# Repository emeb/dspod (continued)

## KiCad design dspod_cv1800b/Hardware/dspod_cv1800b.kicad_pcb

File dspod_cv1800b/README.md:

# dspod_cv1800b

The dspod_cv1800b is a daughterboard comprising a Sophgo/CVItek CV1800B Linux SoC with 64MB RAM, SD card interface, USB and GPIO + audio I/O.

## Abstract

This project was inspired by the release of the Milk-V Duo development board for the Sophgo/CVItek CV1800B SoC back in late 2023. The main chip is a 1GHz dual-core RISC-V system with integrated DRAM in a DIY-friendly 68-pin QFN package that would allow me to build a single-board audio DSP module at low cost without needing fancy PCB processes of complex assembly. I spent a fair amount of time exploring the hardware and OS before concluding that I would be able to tweak it to my requirements, but after getting the basic interfaces working on the Duo board it decided to roll my own.

The board is a small 32-pin device with the following features:

* CV1800B Linux SoC
  - 1GHz RISC-V primary CPU
  - 700MHz RISC-V secondary CPU
  - 8051 low-power CPU
  - 64MB SDRAM~~~~
  - 0.5 TOPS NPU
  - 68-pin QFN package
* Micro SD card slot
* USB-C connector
* Nuvoton NAU88C22 stereo codec
* Misc GPIO
  - SPI
  - I2C
  - GPIO
* Four channels of 3.3V multiplexed A/D input

## Design Materials

* [Schematic](./doc/dspod_cv1800b_schematic.pdf) (PDF)
* [Bill of Materials](./doc/dspod_cv1800b_BOM.ods) (in LibreOffice Calc spreadsheet format)

## Hardware

 Schematic and board design were done with Kicad 9.x and the project is available in the [Hardware](./Hardware/) directory.

## Software

The CV1800B SoC runs a Buildroot / Busybox version of Linux based on a 5.10 kernel
with vendor-customized extensions (not upstreamed). The vendor SDK is freely
available here [Milk-V SDK V2](https://github.com/milkv-duo/duo-buildroot-sdk-v2)

I've customized the kernel with drivers and device-tree configurations that are
specific to this board. My fork of the SDK is here
[Customize kernel SDK](https://github.com/emeb/duo-buildroot-sdk-v2/tree/audio_board)

Additionally, there is a user-space application that provides the UI for the board
along with drivers for the audio codec and 4-channel ADC - find the source here
[dspod app](https://github.com/emeb/duo-examples/tree/main/dspod_app)

## Results

Building an audio DSP module based on the CV1800B SoC was the primary motivation for the dspod project so this 'pod' was the first one that got the full suite of features implemented. The dspod_app software mentioned above has all the features working:

- Stereo audio I/O

- 4 channel CV input

- LCD + encoder based UI

Getting all this working under the Milk-V SDK V2 has been an interesting experience. A few of the things I learned:

#### Audio I/O

This required a fair bit of effort because the pins on the SoC used for I2S audio are the same ones used by the ethernet port, so there was a lot of fiddling around with U-Boot pinmuxing and hidden, poorly-documented control registers to switch those pins over to I2S function. Additionally the I2S MCLK needed by the codec chip had to be stolen from another pin that appeared to be in use (it actually wasn't) and that also required some careful reading of the SoC reference manual to determine that the clock on that pin would actually work. There wasn't really much in the way of kernel shenannigans necessary, but I did have multiple iterations of fiddling with Device Tree to get the I2S drivers hooked up properly.

Eventually I got it all working and it's been very reliable since then. The low-level SoC audio device drivers have been trouble-free and accessing them via ALSA works just like it does on other embedded Linux platforms I've worked with.

#### ADC

I decided to use the on-chip ADC for sampling the four control voltage channels that the dspod design needs, but only two of the three possible channels are brought out to pins on the SoC so an external analog multiplexer was needed. The kernel driver for the ADC is available in both the V1 and V2 SDKs and there’s a nice example available as well so I was able to get it running and learned a few things:

- The existing kernel driver is incomplete - it has interfaces for both the usual char device in the /dev directory and a sysfs entry, but the char device read() function will not work as it doesn’t pass its value back to the caller’s buffer. The sysfs show() function on the other hand returns its value as an ASCII string with a decimal numeric value which is easy to read when you just ‘cat’ the file from the command line but requires you to convert it back to an integer so it’s a bit cumbersome to use within a program.
- The read() and show() functions are similar in that they trigger a conversion and then wait while the ADC is busy before reading the result and returning it. The problem here is that they busywait inside a spinlock_irqsave() so the entire kernel is blocked for 20us while waiting for the conversion. This may be OK if you’re only doing conversions occasionally, but it can seriously hamper performance if conversions are requested frequently.

Because of these issues, I’ve modified the driver to get the read() operation to return a binary value and also digging deeper into how to avoid hogging the system during conversions. There is an IRQ available for the end-of-conversion and I use that, along with delay functions that yield to the kernel scheduler to avoid the use of spinlocks. I’ve also added some logic to control the external analog MUX via GPIO directly from the driver and this is working well.

The hardware aspect of the ADC seems fine - the datasheet doesn’t go into much detail how it works, but from the register map I’ve been able to infer a lot of the details and it seems sane. Overall performance of the converter isn’t great however - I see a fair amount of sample-to-sample noise with a standard deviation of about 5 lsbs near max input range but I suppose that’s to be expected on a complex SoC like this and by applying some heavy filtering in software the results are usable if not particularly accurate. I'm pretty sure this noise is inherent in the hardware as I see similar behavior on the Milk-V Duo board.

#### Encoder

The rotary encoder with pushbutton was a breeze to connect. Some simple additions to the Device tree had it working with no drama and the user-space interface via input events is easy to use and well described.

#### LCD

The dspod module provides a SPI-connected 320x170 IPS LCD based on the ST7789 controller chip. The display is sharp and bright with a good viewing angle and is well supported by the Linux kernel 'fbtft' driver (after some minor modifications to the way the reset line is driven). Getting it working requires a small amount of Device Tree work but for the most part that was not too difficult to set up. Accessing the display from user space is straight-forward and well described with example code from various demos on the internet so I had no difficulty creating a shim layer to work with my personal lightweight graphics suite that allows basic drawing primitives and color manipulation.

Creating a responsive user interface on top of this graphics layer was not difficult, but running it in real-time with the audio and ADC drivers running simultaneously did reveal some "non-ideal behavior" - making near-simultaneous changes to the display buffer in regions that are widely separated in pixel distance can result in significant "behind-the scenes" activity within the fbdev kernel driver as it attempts to update large portions of the display. I found that restricting the amount of screen real-estate that is updated at one time reduced the overall CPU load considerably - just insert some delay time between drawing operations to allow smaller regions to be updated.

#### DSP performance

The proof of the pudding is in the way this system handles the DSP needed for generating audio effects. I have a large library of effects from previous work I've done in the field so I set about trying them out on this system.

###### Time Domain

I "ported" most of my library of interesting time-domain audio effects over to this environment, including the following:

- "Clean delay" - delay with no resampling, just crossfade splicing as the delay is changed.

- "Resampled delay" - delay with sinc-based resampling over an 8:1 range for FM effects.

- Frequency shifter - Bode style I/Q modulation with Hilbert transform filters for generating 90deg phase shifts in real signals for non-harmonically scaled changes in frequency.

- Interpolating delay - similar to clean delay but with inter-sample interpolation and fractional delay values lag-filtered to prevent glitching.

- Phaser - all-pass filter banks for group-delay variations with movable notches.

- Flanger - short fractional delays for group-delay variations with movable notches.

- Pitch shifter - granular delays with variable playback ratios for harmonic-scaled changes in frequency.

- Reverbs - several different types, including an emulation of the venerable MIDIverb for algorithmic simulations of natural spaces.

All of these effects worked as expected with no noticeable glitching or discontiuities in the audio caused by background processes in the Linux operating system and typical CPU loading seen during the worst-case reverb algorithms was about 15%.

###### Frequency Domain

Frequency (or "Spectral") effects rely on the Fast-Fourier Transform (FFT) to convert audio samples into 'bins' of discrete frequency magnitude and phase. The FFT is a fairly math-intensive algorithm and for every buffer of audio it's necessary to perform a forward and reverse transform with the unique spectral algorithm sandwiched between the two. I have a collection of interesting algorithms based on a method called "phase vocoder" that were developed on the [Synthesis Technology - Eurorack E520](https://synthtech.com/eurorack/E520/) and run on the [STM32H743](https://www.st.com/en/microcontrollers-microprocessors/stm32h743-753.html) MCU (a 480MHz Arm Cortex M7 CPU) using the FFT algorithms provided by the Arm CMSIS DSP library. The CMSIS FFT will not run on the CV1800B SoC so I needed to find an alternative and after some research I settled on the [pffft](https://bitbucket.org/jpommier/pffft/src/master/) open-source FFT library which has a reputation for reasonably good performance.

I was able to bring the basic transform processing up on the CV1800B under Linux without difficulty and some benchmarking suggested the 4096-point transform I needed would run in about 1ms - well within the 10ms/buffer that I had available. Given two transforms, the phase vocoder and any unique processing required it seemed there would be enough CPU cycles to get some spectral effects going and the load calculations in my audio test harness showed that basic forward + reverse transforms were taking about 27% of the CPU. Unfortunately the combination of all the I/O, UI and DSP plus background processing for the whole system pushed the total load to over 50% which caused time-critical audio I/O processing to miss its schedule and quickly hang the processor.

Things were looking pretty grim for a while and it seemed like there was no way to get my frequency domain algorithms working on this platform but then an old friend with vastly more experience in embedded Linux came to the rescue. Vlad of [VPME.de](https://vpme.de/) has worked on consumer-grade Linux-based media players and suggested some simple tweaks to the way I was handling my audio thread that boosted its priority above the other things going on and I've now had CPU loads in excess of 50% running for hours without errors. Experience counts!

###### FFT optimization

Initially I had chosen pffft to handle the transforms required for spectral effects, partly because it was well regarded in the open source community, but also because it had SIMD support for several architectures (x86, Arm NEON and PPC Altivec) which led me to believe that it would be easily converted to the RISC-V vector extensions aka [RVV](https://riscv.org/wp-content/uploads/2024/12/15.20-15.55-18.05.06.VEXT-bcn-v1.pdf) which are available on the CV1800B SoC. During testing of pffft I saw approx 30% speedup on x86 when enabling SIMD and was hoping for similar gains with RVV. Unfortunately, the architecture of RVV is sufficiently different from older SIMD implementations that adding it to pffft would have been a large undertaking so instead I looked at simpler FFT libraries that might be more easily modified. After hunting for a while I came back to the original Arm CMSIS DSP library that had been used on the STM32. Benchmarking these against pffft I discovered that for a 4k transform, the radix-4 core with loop unrolling enabled provides about a 30% improvement. Starting with this I experimented with some simple vector optimizations and found that the scalar math used in the radix-4 butterfly was already highly streamlined and my attempts to vectorize it just made it worse. As it stands now I'm seeing the 4k FFT/IFFT running in under 600us which is fast enough to support the spectral effects with sufficient headroom.

###### DSP Summary

With proper understanding of the finer points of Linux userspace coding, the CV1800B SoC under Linux works fine for audio effects in both time and frequency domains. There are still some optimizations that may help to attain even greater processor loads than those seen on the simpler frequency domain algorithms I've tested so far:

- Explore further ways to optimize the FFT algorithm to take advantage of RVV. My first forays into this were naive and didn't pan out, but more clever approaches might improve matters. There have been reports that RVV could provide significant gains for FFTs, but details of these studies are not publicly available at this time.

- Study the possibilities of using the NPU provided on the SoC. The CV1800B has a 0.5 TOPS neural processing unit that supports int8 data. While it's primarily intended for video analysis tasks, with sufficiently clever handling it might be applied to audio DSP as well. There is very little documentation available, but plenty of source code for the examples provided by the manufacturer.

- Move the DSP operations onto the currently unused secondary RISC-V core. That core runs at only 700MHz but would be completely free of any other critical loads beyond handling the crucial computations and so might provide an overall performance boost.

- Abandon Linux altogether and run "bare metal" - there are already some open-source attempts to create a build environment to explore this option. It will be an uphill battle due to lack of comprehensive documentation on the hardware resources, but if possible would lead to the most optimum environment for running realtime DSP.

I'll continue to pursue these and other avenues to improve the situation on the CV1800B.

#### Wrap up

The dspod_cv1800b board shows that an inexpensive commodity SoC targeted at consumer-grade IoT applications can perform well for audio effects with decent quality and an inexpensive price point. Although the manufacturer has recently announced the chip is no longer being sold (EOL), there are other parts in the family that are sufficiently similar that this effort may still be useful on future hardware.

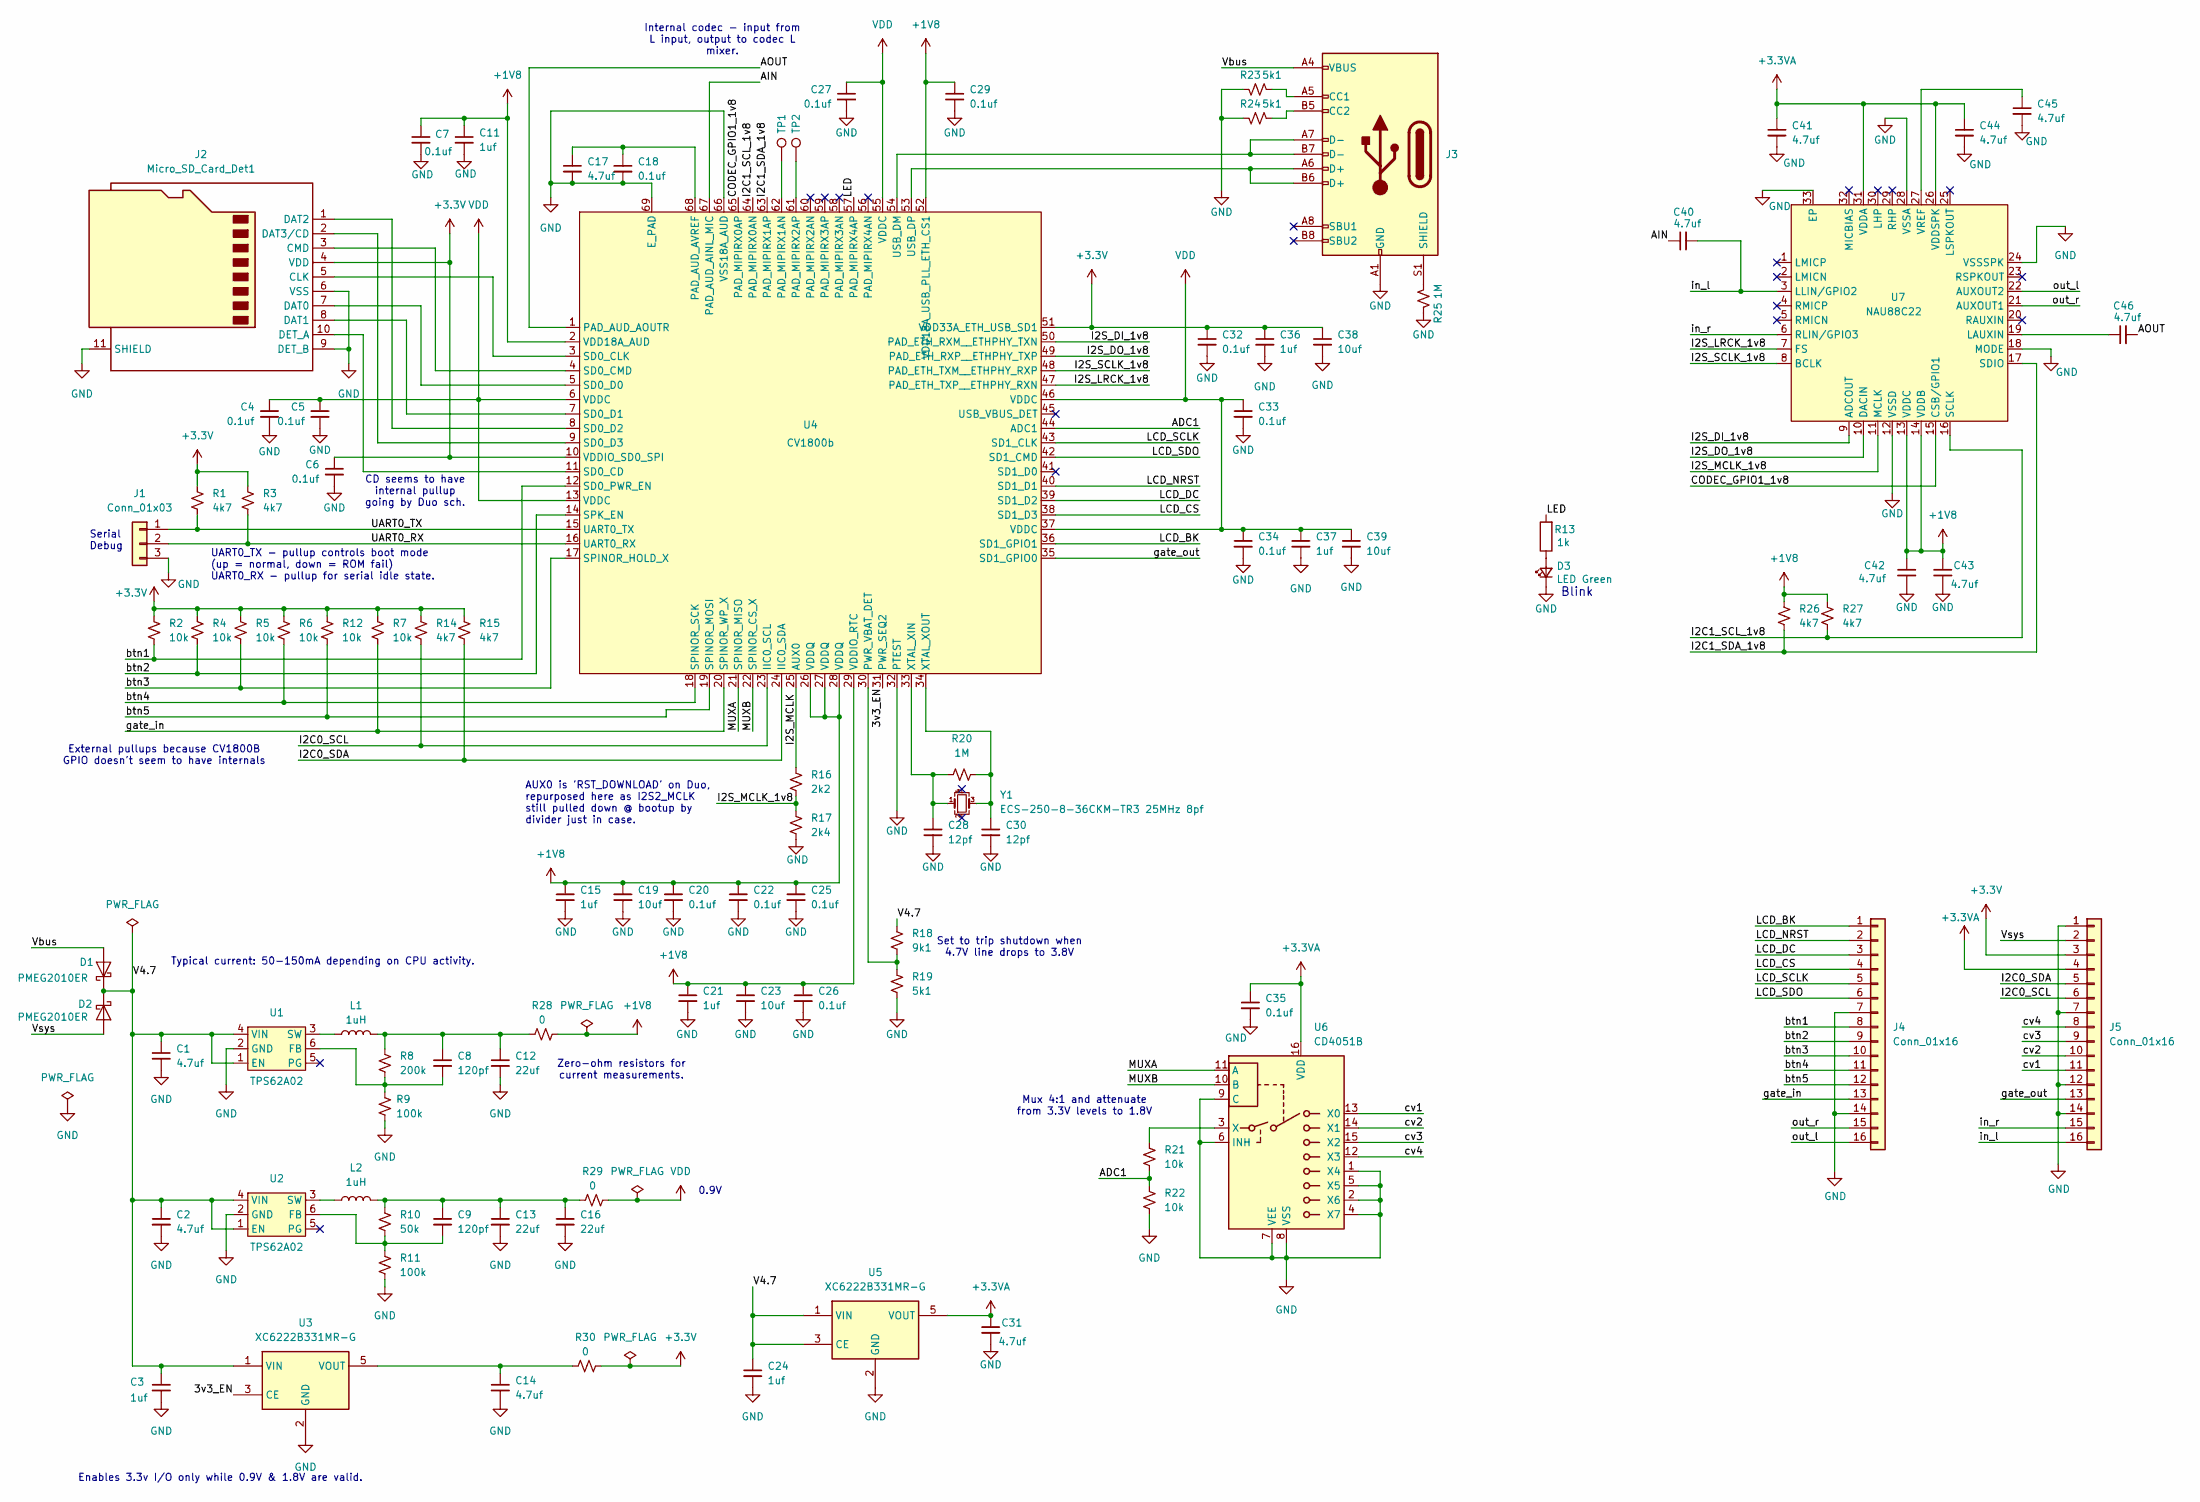
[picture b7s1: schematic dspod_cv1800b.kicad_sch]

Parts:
C1, C2, C14, C17, C31, C40, C41, C42, C43, C44, C45, C46: 4.7uf; C_0402_1005Metric
C3, C11, C15, C21, C24, C36, C37: 1uf; C_0402_1005Metric
C4, C5, C6, C7, C18, C20, C22, C25, C26, C27, C29, C32, C33, C34, C35: 0.1uf; C_0402_1005Metric
C8, C9: 120pf; C_0402_1005Metric
C12, C13, C16: 22uf; C_0805_2012Metric
C19, C23, C38, C39: 10uf; C_0805_2012Metric
C28, C30: 12pf; C_0402_1005Metric
D1, D2: PMEG2010ER; D_SOD-123F
D3: LED Green; LED_0603_1608Metric
J1: Conn_01x03; PinHeader_1x03_P2.54mm_Vertical
J2: Micro_SD_Card_Det1; micro_sd_molex_1040310-811
J3: USB_C_Receptacle_USB2.0; USB_C_Receptacle_HRO_TYPE-C-31-M-12
J4, J5: Conn_01x16; PinHeader_1x16_P2.54mm_Vertical
L1, L2: 1uH; L_1210_3225Metric
R1, R3, R14, R15, R26, R27: 4k7; R_0402_1005Metric
R2, R4, R5, R6, R7, R12, R21, R22: 10k; R_0402_1005Metric
R8: 200k; R_0402_1005Metric
R9, R11: 100k; R_0402_1005Metric
R10: 50k; R_0402_1005Metric
R13: 1k; R_0402_1005Metric
R16: 2k2; R_0402_1005Metric
R17: 2k4; R_0402_1005Metric
R18: 9k1; R_0402_1005Metric
R19, R23, R24: 5k1; R_0402_1005Metric
R20, R25: 1M; R_0402_1005Metric
R28, R29, R30: 0; R_0402_1005Metric
TP1, TP2: TestPoint_Pad_D1.0mm
U1, U2: TPS62A02; SOT-23-6
U3, U5: XC6222B331MR-G; SOT-23-5
U4: CV1800b; QFN-68-1EP_7x7mm_P0.35mm_EP5.7x5.7mm
U6: CD4051B; DHVQFN-16-1EP_2.5x3.5mm_P0.5mm_EP1x2mm
U7: NAU88C22; QFN-32-1EP_5x5mm_P0.5mm_EP3.1x3.1mm
Y1: ECS-250-8-36CKM-TR3 25MHz 8pf; Crystal_SMD_2520-4Pin_2.5x2.0mm

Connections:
+1V8: C7.1, C11.1, C15.1, C19.1, C20.1, C21.1, C22.1, C23.1, C25.1, C26.1, C29.1, C42.1, C43.1, R26.2, R27.2, R28.1, U4.2 (VDD18A_AUD), U4.26 (VDDQ), U4.27 (VDDQ), U4.28 (VDDQ), U4.29 (VDDIO_RTC), U4.52 (VDD18A_USB_PLL_ETH_CS1), U7.13 (VDDC), U7.14 (VDDB)
+3.3V: C6.1, C32.1, C36.1, C38.1, J2.4 (VDD), J5.3, R1.2, R2.2, R3.2, R4.2, R5.2, R6.2, R7.2, R12.2, R14.2, R15.2, R30.1, U4.10 (VDDIO_SD0_SPI), U4.51 (VDD33A_ETH_USB_SD1)
+3.3VA: C31.1, C35.1, C41.1, C44.1, J5.4, U5.5 (VOUT), U6.16 (VDD), U7.26 (VDDSPK), U7.31 (VDDA)
/3v3_EN: U3.3 (CE), U4.31 (PWR_SEQ2)
/ADC1: R21.1, R22.2, U4.44 (ADC1)
/AIN: C40.1, U4.67 (PAD_AUD_AINL_MIC)
/AOUT: C46.2, U4.1 (PAD_AUD_AOUTR)
/CODEC_GPIO1_1v8: U4.65 (PAD_MIPIRX0AP), U7.15 (CSB/GPIO1)
/I2C0_SCL: J5.6, R14.1, U4.23 (IIC0_SCL)
/I2C0_SDA: J5.5, R15.1, U4.24 (IIC0_SDA)
/I2C1_SCL_1v8: R27.1, U4.64 (PAD_MIPIRX0AN), U7.16 (SCLK)
/I2C1_SDA_1v8: R26.1, U4.63 (PAD_MIPIRX1AP), U7.17 (SDIO)
/I2S_DI_1v8: U4.50 (PAD_ETH_RXM__ETHPHY_TXN), U7.9 (ADCOUT)
/I2S_DO_1v8: U4.49 (PAD_ETH_RXP__ETHPHY_TXP), U7.10 (DACIN)
/I2S_LRCK_1v8: U4.47 (PAD_ETH_TXP__ETHPHY_RXN), U7.7 (FS)
/I2S_MCLK: R16.2, U4.25 (AUX0)
/I2S_MCLK_1v8: R16.1, R17.2, U7.11 (MCLK)
/I2S_SCLK_1v8: U4.48 (PAD_ETH_TXM__ETHPHY_RXP), U7.8 (BCLK)
/LCD_BK: J4.1, U4.36 (SD1_GPIO1)
/LCD_CS: J4.4, U4.38 (SD1_D3)
/LCD_DC: J4.3, U4.39 (SD1_D2)
/LCD_NRST: J4.2, U4.40 (SD1_D1)
/LCD_SCLK: J4.5, U4.43 (SD1_CLK)
/LCD_SDO: J4.6, U4.42 (SD1_CMD)
/LED: R13.2, U4.57 (PAD_MIPIRX4AP)
/MUXA: U4.21 (SPINOR_MISO), U6.11 (A)
/MUXB: U4.22 (SPINOR_CS_X), U6.10 (B)
/UART0_RX: J1.2, R3.1, U4.16 (UART0_RX)
/UART0_TX: J1.1, R1.1, U4.15 (UART0_TX)
/V4.7: C1.1, C2.1, C3.1, C24.1, D1.1 (K), D2.1 (K), R18.2, U1.1 (EN), U1.4 (VIN), U2.1 (EN), U2.4 (VIN), U3.1 (VIN), U5.1 (VIN), U5.3 (CE)
/Vbus: D1.2 (A), J3.A4 (VBUS), J3.A9 (VBUS), J3.B4 (VBUS), J3.B9 (VBUS)
/Vsys: D2.2 (A), J5.2
/btn1: J4.8, R2.1, U4.12 (SD0_PWR_EN)
/btn2: J4.9, R4.1, U4.14 (SPK_EN)
/btn3: J4.10, R5.1, U4.17 (SPINOR_HOLD_X)
/btn4: J4.11, R6.1, U4.18 (SPINOR_SCK)
/btn5: J4.12, R12.1, U4.19 (SPINOR_MOSI)
/cv1: J5.11, U6.13 (X0)
/cv2: J5.10, U6.14 (X1)
/cv3: J5.9, U6.15 (X2)
/cv4: J5.8, U6.12 (X3)
/gate_in: J4.13, R7.1, U4.20 (SPINOR_WP_X)
/gate_out: J5.13, U4.35 (SD1_GPIO0)
/in_l: C40.2, J5.16, U7.3 (LLIN/GPIO2)
/in_r: J5.15, U7.6 (RLIN/GPIO3)
/out_l: J4.16, U7.22 (AUXOUT2)
/out_r: J4.15, U7.21 (AUXOUT1)
GND: C1.2, C2.2, C3.2, C4.2, C5.2, C6.2, C7.2, C11.2, C12.2, C13.2, C14.2, C15.2, C16.2, C17.2, C18.2, C19.2, C20.2, C21.2, C22.2, C23.2, C24.2, C25.2, C26.2, C27.2, C28.2, C29.2, C30.2, C31.2, C32.2, C33.2, C34.2, C35.2, C36.2, C37.2, C38.2, C39.2, C41.2, C42.2, C43.2, C44.2, C45.2, D3.1 (K), J1.3, J2.6 (VSS), J2.9 (DET_B), J2.11 (SHIELD), J3.A1 (GND), J3.A12 (GND), J3.B1 (GND), J3.B12 (GND), J4.7, J4.14, J5.1, J5.7, J5.12, J5.14, R9.1, R11.1, R17.1, R19.1, R22.1, R23.1, R24.1, R25.1, U1.2 (GND), U2.2 (GND), U3.2 (GND), U4.32 (PTEST), U4.66 (VSS18A_AUD), U4.69 (E_PAD), U5.2 (GND), U6.1 (X4), U6.2 (X6), U6.4 (X7), U6.5 (X5), U6.6 (INH), U6.7 (VEE), U6.8 (VSS), U6.9 (C), U7.12 (VSSD), U7.18 (MODE), U7.24 (VSSSPK), U7.28 (VSSA), U7.33 (EP)
unnamed: C8.1, C12.1, L1.2, R8.2, R28.2
unnamed: C9.1, C13.1, C16.1, L2.2, R10.2, R29.2
unnamed: D3.2 (A), R13.1
unnamed: J2.5 (CLK), U4.3 (SD0_CLK)
unnamed: J2.3 (CMD), U4.4 (SD0_CMD)
unnamed: J2.7 (DAT0), U4.5 (SD0_D0)
unnamed: J2.8 (DAT1), U4.7 (SD0_D1)
unnamed: J2.1 (DAT2), U4.8 (SD0_D2)
unnamed: J2.2 (DAT3/CD), U4.9 (SD0_D3)
unnamed: J2.10 (DET_A), U4.11 (SD0_CD)
unnamed: J3.A5 (CC1), R23.2
unnamed: J3.B5 (CC2), R24.2
unnamed: J3.S1 (SHIELD), R25.2
unnamed: C8.2, R8.1, R9.2, U1.6 (FB)
unnamed: L1.1, U1.3 (SW)
unnamed: C9.2, R10.1, R11.2, U2.6 (FB)
unnamed: L2.1, U2.3 (SW)
unnamed: C14.1, R30.2, U3.5 (VOUT)
unnamed: C17.1, C18.1, U4.68 (PAD_AUD_AVREF)
unnamed: TP1.1, U4.62 (PAD_MIPIRX1AN)
unnamed: TP2.1, U4.61 (PAD_MIPIRX2AP)
unnamed: R18.1, R19.2, U4.30 (PWR_VBAT_DET)
unnamed: J3.A7 (D-), J3.B7 (D-), U4.54 (USB_DM)
unnamed: J3.A6 (D+), J3.B6 (D+), U4.53 (USB_DP)
unnamed: C28.1, R20.1, U4.33 (XTAL_XIN), Y1.1
unnamed: C30.1, R20.2, U4.34 (XTAL_XOUT), Y1.3
unnamed: R21.2, U6.3 (X)
unnamed: C46.1, U7.19 (LAUXIN)
unnamed: C45.1, U7.27 (VREF)
VDD: C4.1, C5.1, C27.1, C33.1, C34.1, C37.1, C39.1, R29.1, U4.6 (VDDC), U4.13 (VDDC), U4.37 (VDDC), U4.46 (VDDC), U4.55 (VDDC)

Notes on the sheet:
Mux 4:1 and attenuate from 3.3V levels to 1.8V
UART0_TX - pullup controls boot mode (up = normal, down = ROM fail) UART0_RX - pullup for serial idle state.
Zero-ohm resistors for current measurements.
Blink
Set to trip shutdown when 4.7V line drops to 3.8V
External pullups because CV1800B GPIO doesn't seem to have internals
AUX0 is 'RST_DOWNLOAD' on Duo, repurposed here as I2S2_MCLK still pulled down @ bootup by divider just in case.
Serial Debug
Enables 3.3v I/O only while 0.9V & 1.8V are valid.
Internal codec - input from L input, output to codec L mixer.
0.9V
Typical current: 50-150mA depending on CPU activity.
CD seems to have internal pullup going by Duo sch.

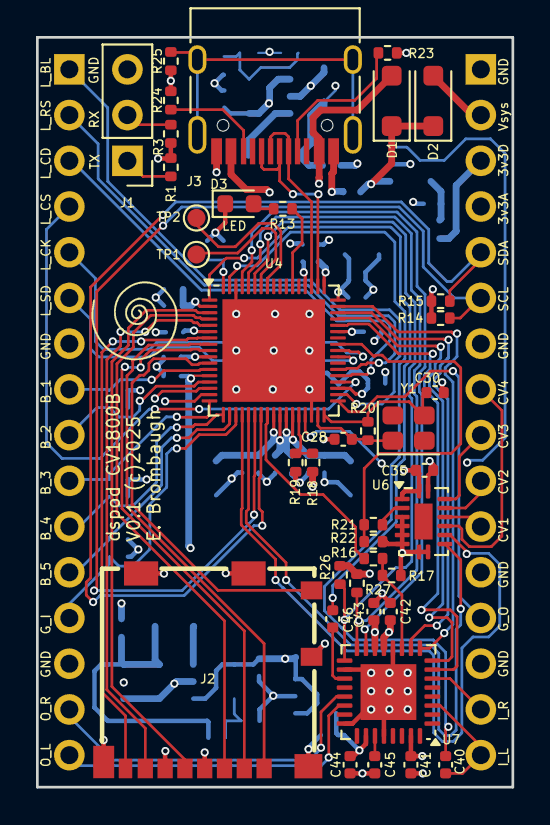
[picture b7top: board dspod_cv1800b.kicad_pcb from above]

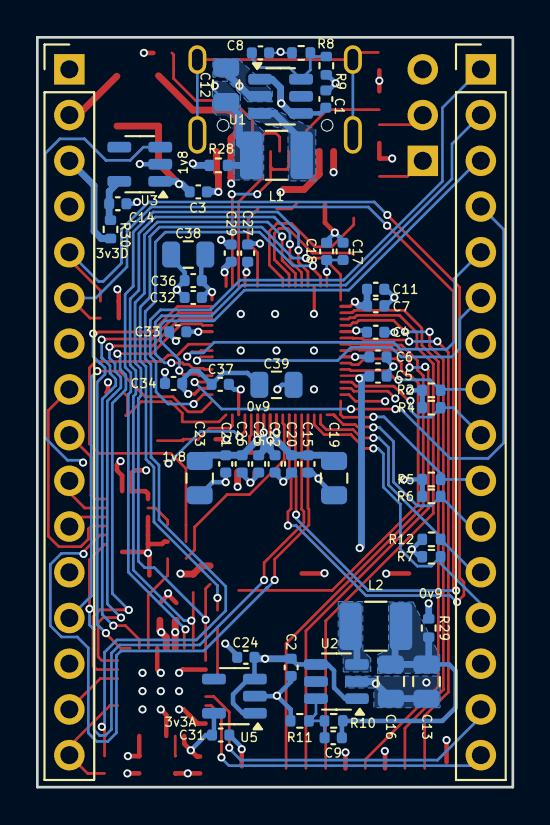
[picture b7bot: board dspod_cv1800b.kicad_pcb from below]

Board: 4 copper layers, 26.4 x 41.7 mm, 96 parts (56 on the bottom side), 78 nets.

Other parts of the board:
Ref**: Val**; avatar_small

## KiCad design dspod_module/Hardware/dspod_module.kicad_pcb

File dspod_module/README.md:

# dspod_module
This directory contains the design collateral for the dspod_module

## Abstract
The dspod_module is a Eurorack module that acts as a motherboard / carrier for
the various dspod daughterboards. It provides the following resources:
* Eurorack front panel
* Eurorack power supply with 5V, and +/-12V
* 320 x 170 IPS LCD with ST7789 controller in SPI mode
* 4x 3.3V CV interfaces with 3.5mm input jacks and offset pots
* 2x +/-7V stereo audio inputs
* 2x +/-7V stereo audio outputs
* 1x trigger/gate input with 3.3V logic level buffer
* 1x trigger/gate output with 3.3V -> 5V logic level buffer
* Quadrature rotary encoder w/ pushbutton.

## Design
The design materials are available in Kicad 9.0 format, including schematic and
PCB layout.

* [schematic](./doc/dspod_module_schematic.pdf)

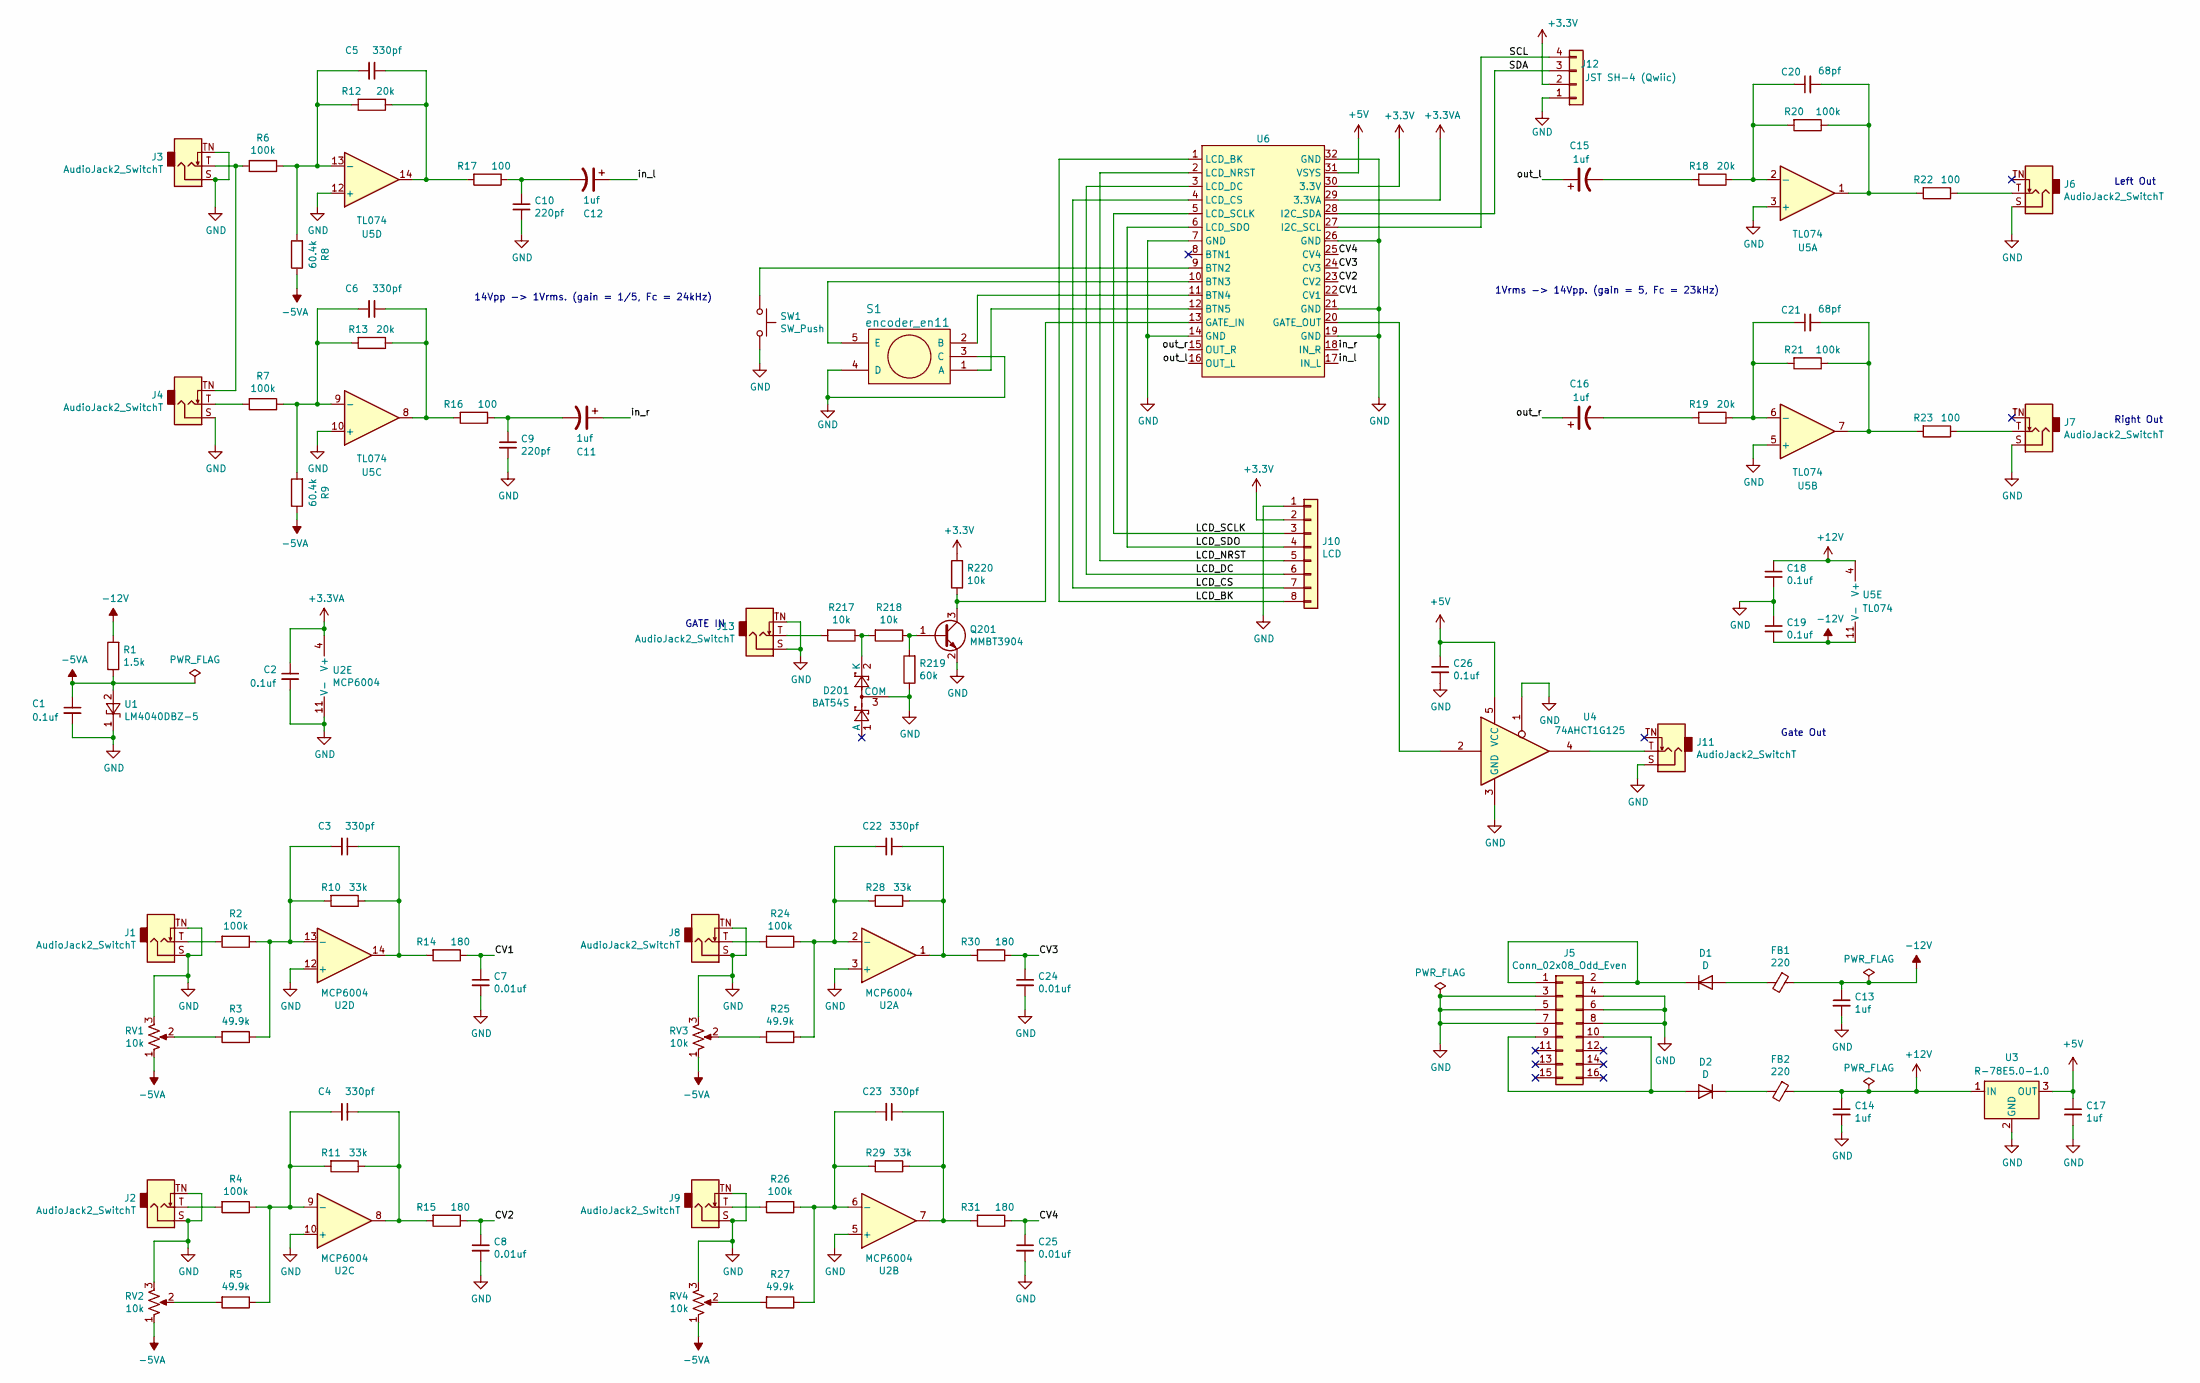
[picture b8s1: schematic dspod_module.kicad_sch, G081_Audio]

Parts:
C1, C2, C18, C19, C26: 0.1uf; C_0603_1608Metric
C3, C4, C5, C6, C22, C23: 330pf; C_0603_1608Metric
C7, C8, C24, C25: 0.01uf; C_0603_1608Metric
C9, C10: 220pf; C_0603_1608Metric
C11, C12, C15, C16: 1uf; CP_Elec_4x5.3
C13, C14, C17: 1uf; C_0603_1608Metric
C20, C21: 68pf; C_0603_1608Metric
D1, D2: D; D_SMA
D201: BAT54S; SOT-23
FB1, FB2: 220; C_0805_2012Metric
J1, J2, J3, J4, J6, J7, J8, J9, J11, J13: AudioJack2_SwitchT; Jack_3.5mm_QingPu_WQP-PJ398SM_Vertical_CircularHoles
J5: Conn_02x08_Odd_Even; con16_2X8_S4_TEC
J10: LCD; 1.9_IPS_LCD
J12: JST SH-4 (Qwiic); JST_SH_SM04B-SRSS-TB_04x1.00mm_Angled
Q201: MMBT3904; SOT-23
R1: 1.5k; R_0603_1608Metric
R2, R4, R6, R7, R20, R21, R24, R26: 100k; R_0603_1608Metric
R3, R5, R25, R27: 49.9k; R_0603_1608Metric
R8, R9: 60.4k; R_0603_1608Metric
R10, R11, R28, R29: 33k; R_0603_1608Metric
R12, R13, R18, R19: 20k; R_0603_1608Metric
R14, R15, R30, R31: 180; R_0603_1608Metric
R16, R17, R22, R23: 100; R_0603_1608Metric
R217, R218, R220: 10k; R_0603_1608Metric
R219: 60k; R_0603_1608Metric
RV1, RV2, RV3, RV4: 10k; Potentiometer_TT_P0915N
S1: encoder_en11; ENC_11
SW1: SW_Push; SW_PUSH_6mm
U1: LM4040DBZ-5; SOT-23
U2: MCP6004; SOIC-14_3.9x8.7mm_P1.27mm
U3: R-78E5.0-1.0; Converter_DCDC_RECOM_R-78E-0.5_THT
U4: 74AHCT1G125; SOT-23-5
U5: TL074; SOIC-14_3.9x8.7mm_P1.27mm
U6: dspod

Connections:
+3.3V: J10.2, J12.2, R220.2, U6.30 (3.3V)
+3.3VA: C2.1, U2.4 (V+), U6.29 (3.3VA)
+5V: C17.1, C26.1, U3.3 (OUT), U4.5 (VCC), U6.31 (VSYS)
+12V: C14.1, C18.1, FB2.1, U3.1 (IN), U5.4 (V+)
-5VA: C1.1, R1.1, R8.1, R9.1, RV1.1, RV2.1, RV3.1, RV4.1, U1.2 (A)
-12V: C13.1, C19.2, FB1.1, R1.2, U5.11 (V-)
/CV1: C7.1, R14.1, U6.22 (CV1)
/CV2: C8.1, R15.1, U6.23 (CV2)
/CV3: C24.1, R30.1, U6.24 (CV3)
/CV4: C25.1, R31.1, U6.25 (CV4)
/LCD_BK: J10.8, U6.1 (LCD_BK)
/LCD_CS: J10.7, U6.4 (LCD_CS)
/LCD_DC: J10.6, U6.3 (LCD_DC)
/LCD_NRST: J10.5, U6.2 (LCD_NRST)
/LCD_SCLK: J10.3, U6.5 (LCD_SCLK)
/LCD_SDO: J10.4, U6.6 (LCD_SDO)
/SCL: J12.4, U6.27 (I2C_SCL)
/SDA: J12.3, U6.28 (I2C_SDA)
/in_l: C12.1, U6.17 (IN_L)
/in_r: C11.1, U6.18 (IN_R)
/out_l: C15.1, U6.16 (OUT_L)
/out_r: C16.1, U6.15 (OUT_R)
GND: C1.2, C2.2, C7.2, C8.2, C9.2, C10.2, C13.2, C14.2, C17.2, C18.2, C19.1, C24.2, C25.2, C26.2, D201.3 (COM), J1.S, J1.TN, J2.S, J2.TN, J3.S, J3.TN, J4.S, J5.3, J5.4, J5.5, J5.6, J5.7, J5.8, J6.S, J7.S, J8.S, J8.TN, J9.S, J9.TN, J10.1, J11.S, J12.1, J13.S, J13.TN, Q201.2 (E), R219.1, RV1.3, RV2.3, RV3.3, RV4.3, S1.3 (C), S1.4 (D), SW1.2, U1.1 (K), U2.3 (+), U2.5 (+), U2.10 (+), U2.11 (V-), U2.12 (+), U3.2 (GND), U4.1, U4.3 (GND), U5.3 (+), U5.5 (+), U5.10 (+), U5.12 (+), U6.7 (GND), U6.14 (GND), U6.19 (GND), U6.21 (GND), U6.26 (GND), U6.32 (GND)
unnamed: C3.1, R10.1, R14.2, U2.14
unnamed: C4.1, R11.1, R15.2, U2.8
unnamed: C5.1, R12.1, R17.2, U5.14
unnamed: C6.1, R13.1, R16.2, U5.8
unnamed: C10.1, C12.2, R17.1
unnamed: C9.1, C11.2, R16.1
unnamed: C15.2, R18.2
unnamed: C16.2, R19.2
unnamed: C20.2, R20.1, R22.2, U5.1
unnamed: C21.2, R21.1, R23.2, U5.7
unnamed: C22.1, R28.1, R30.2, U2.1
unnamed: C23.1, R29.1, R31.2, U2.7
unnamed: D1.2 (A), FB1.2
unnamed: D1.1 (K), J5.1, J5.2
unnamed: D2.2 (A), J5.9, J5.10
unnamed: D2.1 (K), FB2.2
unnamed: D201.2 (K), R217.1, R218.2
unnamed: J1.T, R2.2
unnamed: J2.T, R4.2
unnamed: J3.T, J4.TN, R6.2
unnamed: J4.T, R7.2
unnamed: J6.T, R22.1
unnamed: J7.T, R23.1
unnamed: J8.T, R24.2
unnamed: J9.T, R26.2
unnamed: J11.T, U4.4
unnamed: J13.T, R217.2
unnamed: Q201.1 (B), R218.1, R219.2
unnamed: Q201.3 (C), R220.1, U6.13 (GATE_IN)
unnamed: R3.2, RV1.2
unnamed: R5.2, RV2.2
unnamed: R25.2, RV3.2
unnamed: R27.2, RV4.2
unnamed: S1.1 (A), U6.12 (BTN5)
unnamed: S1.2 (B), U6.11 (BTN4)
unnamed: S1.5 (E), U6.10 (BTN3)
unnamed: C22.2, R24.1, R25.1, R28.2, U2.2 (-)
unnamed: C23.2, R26.1, R27.1, R29.2, U2.6 (-)
unnamed: C4.2, R4.1, R5.1, R11.2, U2.9 (-)
unnamed: C3.2, R2.1, R3.1, R10.2, U2.13 (-)
unnamed: C20.1, R18.1, R20.2, U5.2 (-)
unnamed: C21.1, R19.1, R21.2, U5.6 (-)
unnamed: C6.2, R7.1, R9.2, R13.2, U5.9 (-)
unnamed: C5.2, R6.1, R8.2, R12.2, U5.13 (-)
unnamed: SW1.1, U6.9 (BTN2)
unnamed: U4.2, U6.20 (GATE_OUT)

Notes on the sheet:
14Vpp -> 1Vrms. (gain = 1/5, Fc = 24kHz)
Left Out
Right Out
Gate Out
1Vrms -> 14Vpp. (gain = 5, Fc = 23kHz)
GATE IN

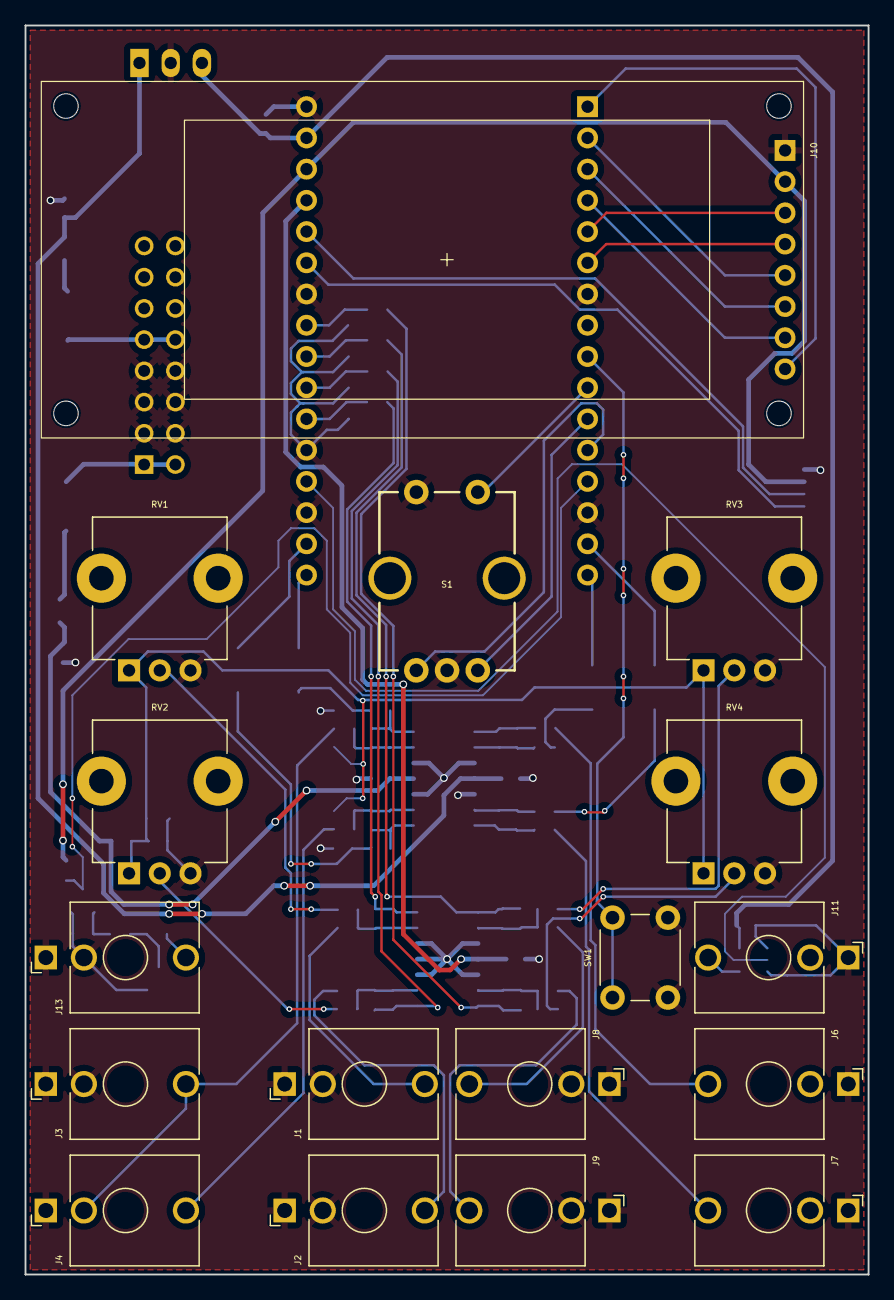
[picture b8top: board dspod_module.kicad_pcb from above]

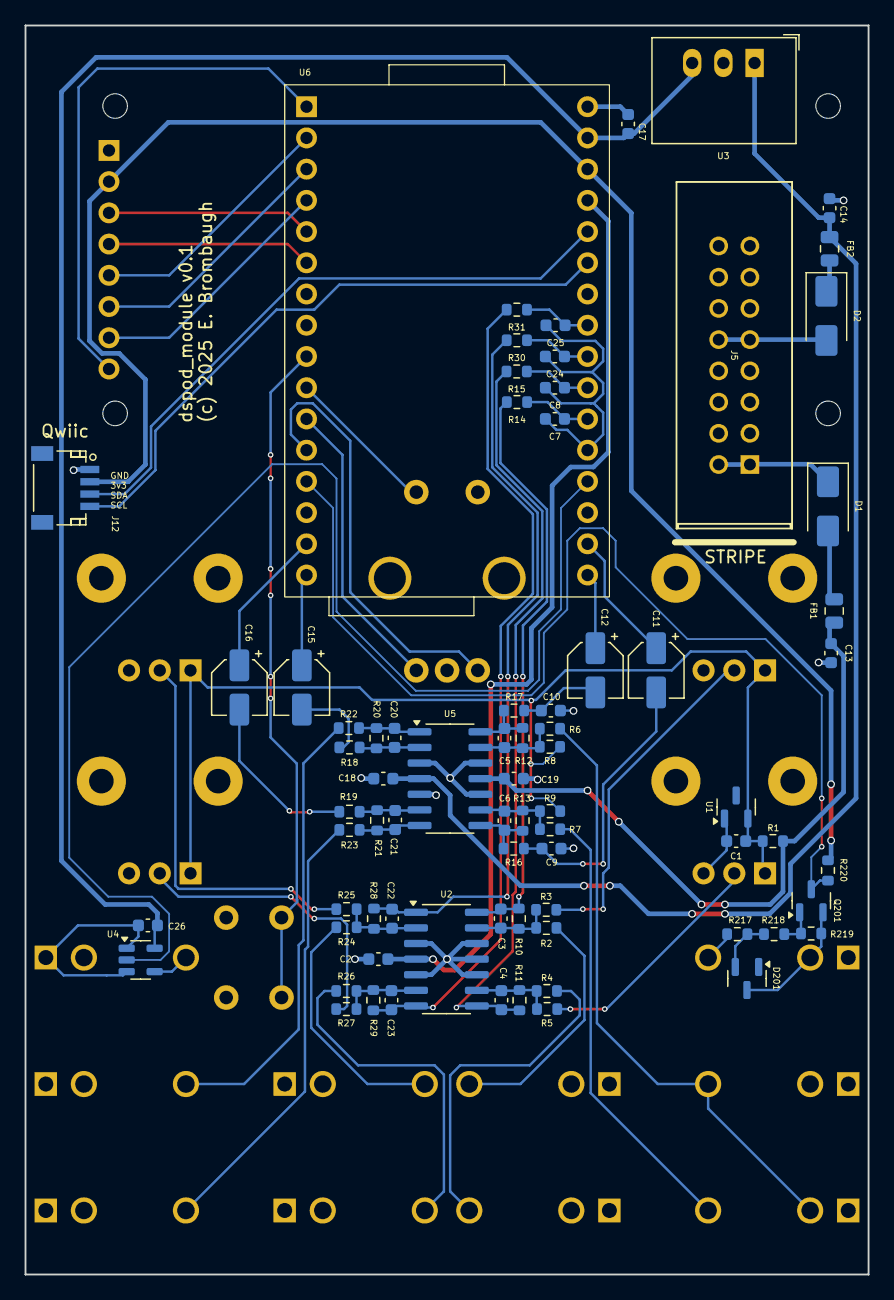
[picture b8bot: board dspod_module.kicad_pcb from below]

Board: 2 copper layers, 68.6 x 101.6 mm, 92 parts (75 on the bottom side), 69 nets.

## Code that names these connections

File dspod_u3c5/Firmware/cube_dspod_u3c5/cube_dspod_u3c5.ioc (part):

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Mcu.Name=STM32U3C5RITx
Mcu.Package=LQFP64
Mcu.UserName=STM32U3C5RITx
PA0.Mode=Audio_ClockInSAI1
PA0.Signal=AUDIOCLK
PA1.Mode=IN4-Single-Ended
PA1.Signal=ADC1_IN4
PA10.Mode=Asynchronous
PA10.Signal=USART1_RX
PA11.Mode=Device
PA11.Signal=USB_DM
PA12.Mode=Device
PA12.Signal=USB_DP
PA13\ (JTMS/SWDIO).Mode=Serial_Wire
PA13\ (JTMS/SWDIO).Signal=DEBUG_JTMS-SWDIO
PA14\ (JTCK/SWCLK).Mode=Serial_Wire
PA14\ (JTCK/SWCLK).Signal=DEBUG_JTCK-SWCLK
PA15\ (JTDI).Mode=NSS_Signal_Hard_Output
PA15\ (JTDI).Signal=SPI3_NSS
PA2.Mode=IN5-Single-Ended
PA2.Signal=ADC1_IN5
PA3.Mode=quad_mode
PA3.Signal=OCTOSPI1_CLK
PA4.Mode=quad_mode
PA4.Signal=OCTOSPI1_NCS
PA6.Mode=OCTOSPI1_IO[3\:0]
PA6.Signal=OCTOSPI1_IO3
PA7.Mode=OCTOSPI1_IO[3\:0]
PA7.Signal=OCTOSPI1_IO2
PA9.Mode=Asynchronous
PA9.Signal=USART1_TX
PB0.Mode=OCTOSPI1_IO[3\:0]
PB0.Signal=OCTOSPI1_IO1
PB1.Mode=OCTOSPI1_IO[3\:0]
PB1.Signal=OCTOSPI1_IO0
PB10.Mode=SAI_A_MasterWithClock
PB10.Signal=SAI1_SCK_A
PB13.Mode=I2C
PB13.Signal=I2C2_SCL
PB14.Mode=I2C
PB14.Signal=I2C2_SDA
PB3\ (JTDO/TRACESWO).Mode=MOD_MDF_CCK0
PB3\ (JTDO/TRACESWO).Signal=ADF1_CCK0
PB4\ (NJTRST).Mode=MOD_ADF_CCK
PB4\ (NJTRST).Signal=ADF1_SDI0
PB5.Mode=SAI_B_SyncSlave
PB5.Signal=SAI1_SD_B
PB8.Mode=SAI_A_MasterWithClock
PB8.Signal=SAI1_MCLK_A
PB9.Mode=SAI_A_MasterWithClock
PB9.Signal=SAI1_FS_A
PC0.Mode=IN1-Single-Ended
PC0.Signal=ADC1_IN1
PC1.Mode=IN2-Single-Ended
PC1.Signal=ADC1_IN2
PC10.Mode=Full_Duplex_Master
PC10.Signal=SPI3_SCK
PC11.Mode=Full_Duplex_Master
PC11.Signal=SPI3_MISO
PC12.Mode=Full_Duplex_Master
PC12.Signal=SPI3_MOSI
PC3.Mode=SAI_A_MasterWithClock
PC3.Signal=SAI1_SD_A
PH0-OSC_IN\ (PH0).Mode=HSE-External-Oscillator
PH0-OSC_IN\ (PH0).Signal=RCC_OSC_IN
PH1-OSC_OUT\ (PH1).Mode=HSE-External-Oscillator
PH1-OSC_OUT\ (PH1).Signal=RCC_OSC_OUT
RCC.HSE_VALUE=16000000
RCC.SYSCLKFreq_VALUE=96000000
board=custom

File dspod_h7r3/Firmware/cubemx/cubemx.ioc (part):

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Mcu.Name=STM32H7R3V8Tx
Mcu.Package=LQFP100
Mcu.UserName=STM32H7R3V8Tx
PA1.GPIOParameters=PinAttribute
PA1.PinAttribute=Boot
PA1.Signal=ADCx_INP1
PA13(JTMS/SWDIO).Mode=Serial_Wire
PA13(JTMS/SWDIO).Signal=DEBUG_JTMS-SWDIO
PA14(JTCK/SWCLK).Mode=Serial_Wire
PA14(JTCK/SWCLK).Signal=DEBUG_JTCK-SWCLK
PA2.GPIOParameters=PinAttribute
PA2.PinAttribute=Boot
PA2.Signal=ADCx_INP14
PA3.GPIOParameters=PinAttribute
PA3.Mode=Master_Clock_Activated
PA3.PinAttribute=Boot
PA3.Signal=I2S6_MCK
PA4.GPIOParameters=PinAttribute
PA4.Mode=Full_Duplex_Master
PA4.PinAttribute=Boot
PA4.Signal=I2S6_WS
PA5.GPIOParameters=PinAttribute
PA5.Mode=Full_Duplex_Master
PA5.PinAttribute=Boot
PA5.Signal=I2S6_CK
PA6.GPIOParameters=PinAttribute
PA6.Mode=Full_Duplex_Master
PA6.PinAttribute=Boot
PA6.Signal=I2S6_SDI
PA7.GPIOParameters=PinAttribute
PA7.Mode=Full_Duplex_Master
PA7.PinAttribute=Boot
PA7.Signal=I2S6_SDO
PB0.GPIOParameters=PinAttribute
PB0.PinAttribute=Boot
PB0.Signal=ADCx_INP9
PB1.GPIOParameters=PinAttribute
PB1.PinAttribute=Boot
PB1.Signal=ADCx_INP5
PB10.GPIOParameters=PinAttribute
PB10.Mode=I2C
PB10.PinAttribute=Boot
PB10.Signal=I2C2_SCL
PB11.GPIOParameters=PinAttribute
PB11.Mode=I2C
PB11.PinAttribute=Boot
PB11.Signal=I2C2_SDA
PB14.GPIOParameters=PinAttribute
PB14.Mode=Asynchronous
PB14.PinAttribute=Boot
PB14.Signal=USART1_TX
PB15.GPIOParameters=PinAttribute
PB15.Mode=Asynchronous
PB15.PinAttribute=Boot
PB15.Signal=USART1_RX
PB3(JTDO/TRACESWO).GPIOParameters=PinAttribute
PB3(JTDO/TRACESWO).Mode=Simplex_Bidirectional_Master
PB3(JTDO/TRACESWO).PinAttribute=Boot
PB3(JTDO/TRACESWO).Signal=SPI3_SCK
PB5.GPIOParameters=PinAttribute
PB5.Mode=Simplex_Bidirectional_Master
PB5.PinAttribute=Boot
PB5.Signal=SPI3_MOSI
PH0-OSC_IN(PH0).Mode=HSE-External-Oscillator
PH0-OSC_IN(PH0).Signal=RCC_OSC_IN
PH1-OSC_OUT(PH1).Mode=HSE-External-Oscillator
PH1-OSC_OUT(PH1).Signal=RCC_OSC_OUT
RCC.HSE_VALUE=12000000
RCC.SYSCLKFreq_VALUE=600000000
RCC.SYSCLKSource=RCC_SYSCLKSOURCE_PLLCLK
board=custom

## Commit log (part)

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2025-09-14 Added MIT license
2025-09-14 Added module info
2025-09-14 expand top-level text
2025-09-14 Added dspod_cv1800b hardware materials
2025-09-14 Update README.md with correct image name
2025-09-14 Added schematic and links to software
2025-09-19 Added RP2350 board
2025-09-19 Delete dspod_rp2350/Firmware/dspod_blinky/build directory
    remove accidentally committed build directory
2025-09-19 Added ESP32S3 board
2025-09-19 fix link in README.md
2025-09-19 Fix some formatting issues
2025-09-19 Added tech details
2025-09-21 add some links, more detail on read/write ops
2025-09-21 Updated README with latest firmware news
2025-09-21 more changes
2025-09-22 Added H7R3 dspod
2025-10-06 Updated FFT stuff
2025-10-14 Added DSPOD APP
2025-10-16 Updated with minor tweaks for release to fab
2025-10-16 Updated docs for release to fab
2025-10-19 Added FFT code for examples
2025-11-06 Added firmware source
2025-11-06 Add details for tools
2025-11-28 Add lcd, encoder. Change OOCD, add main.h to all.
2025-11-29 Add detail to the README
2025-11-29 link firmware to S3GTA in README
2025-11-29 fix malformed links
2025-11-29 Add more text to README
2025-12-01 Added dsp fx app, fix issues in ADC, I2S, XSPI.
2025-12-04 Updated w/ performance info
2026-01-01 Added new content for external flash and TinyUF2
2026-01-03 Added TinyUSB stuff
2026-01-08 Updated READMEs with details on high-speed USB
2026-01-27 Added firmware directory with test code.
2026-01-27 Update README to reflect correct board name
2026-01-27 Fix image reference in README.md
2026-01-27 Revise README with MCU details and future exploration
    Updated README to reflect changes in MCU model and added details about PSRAM usage and future exploration areas.
2026-01-31 Updated images and expanded results text
2026-01-31 Improve formatting in README.md
    Added a line break for better formatting in README.
2026-02-14 Added clock speed observations
2026-03-31 Added dspod_u3c5 project
2026-03-31 Added dspod_up5k project, some cleanups / tweaks.
2026-03-31 Rename project from dspod_h7r3 to dspod_up5k
2026-03-31 Rename project from dspod_h7r3 to dspod_u3c5
2026-03-31 update renders
2026-05-15 Update dspod_u3c5 documentation with latest test results.
2026-05-16 Add firmware, update top-level README
2026-05-16 Added more detail on HSP use
